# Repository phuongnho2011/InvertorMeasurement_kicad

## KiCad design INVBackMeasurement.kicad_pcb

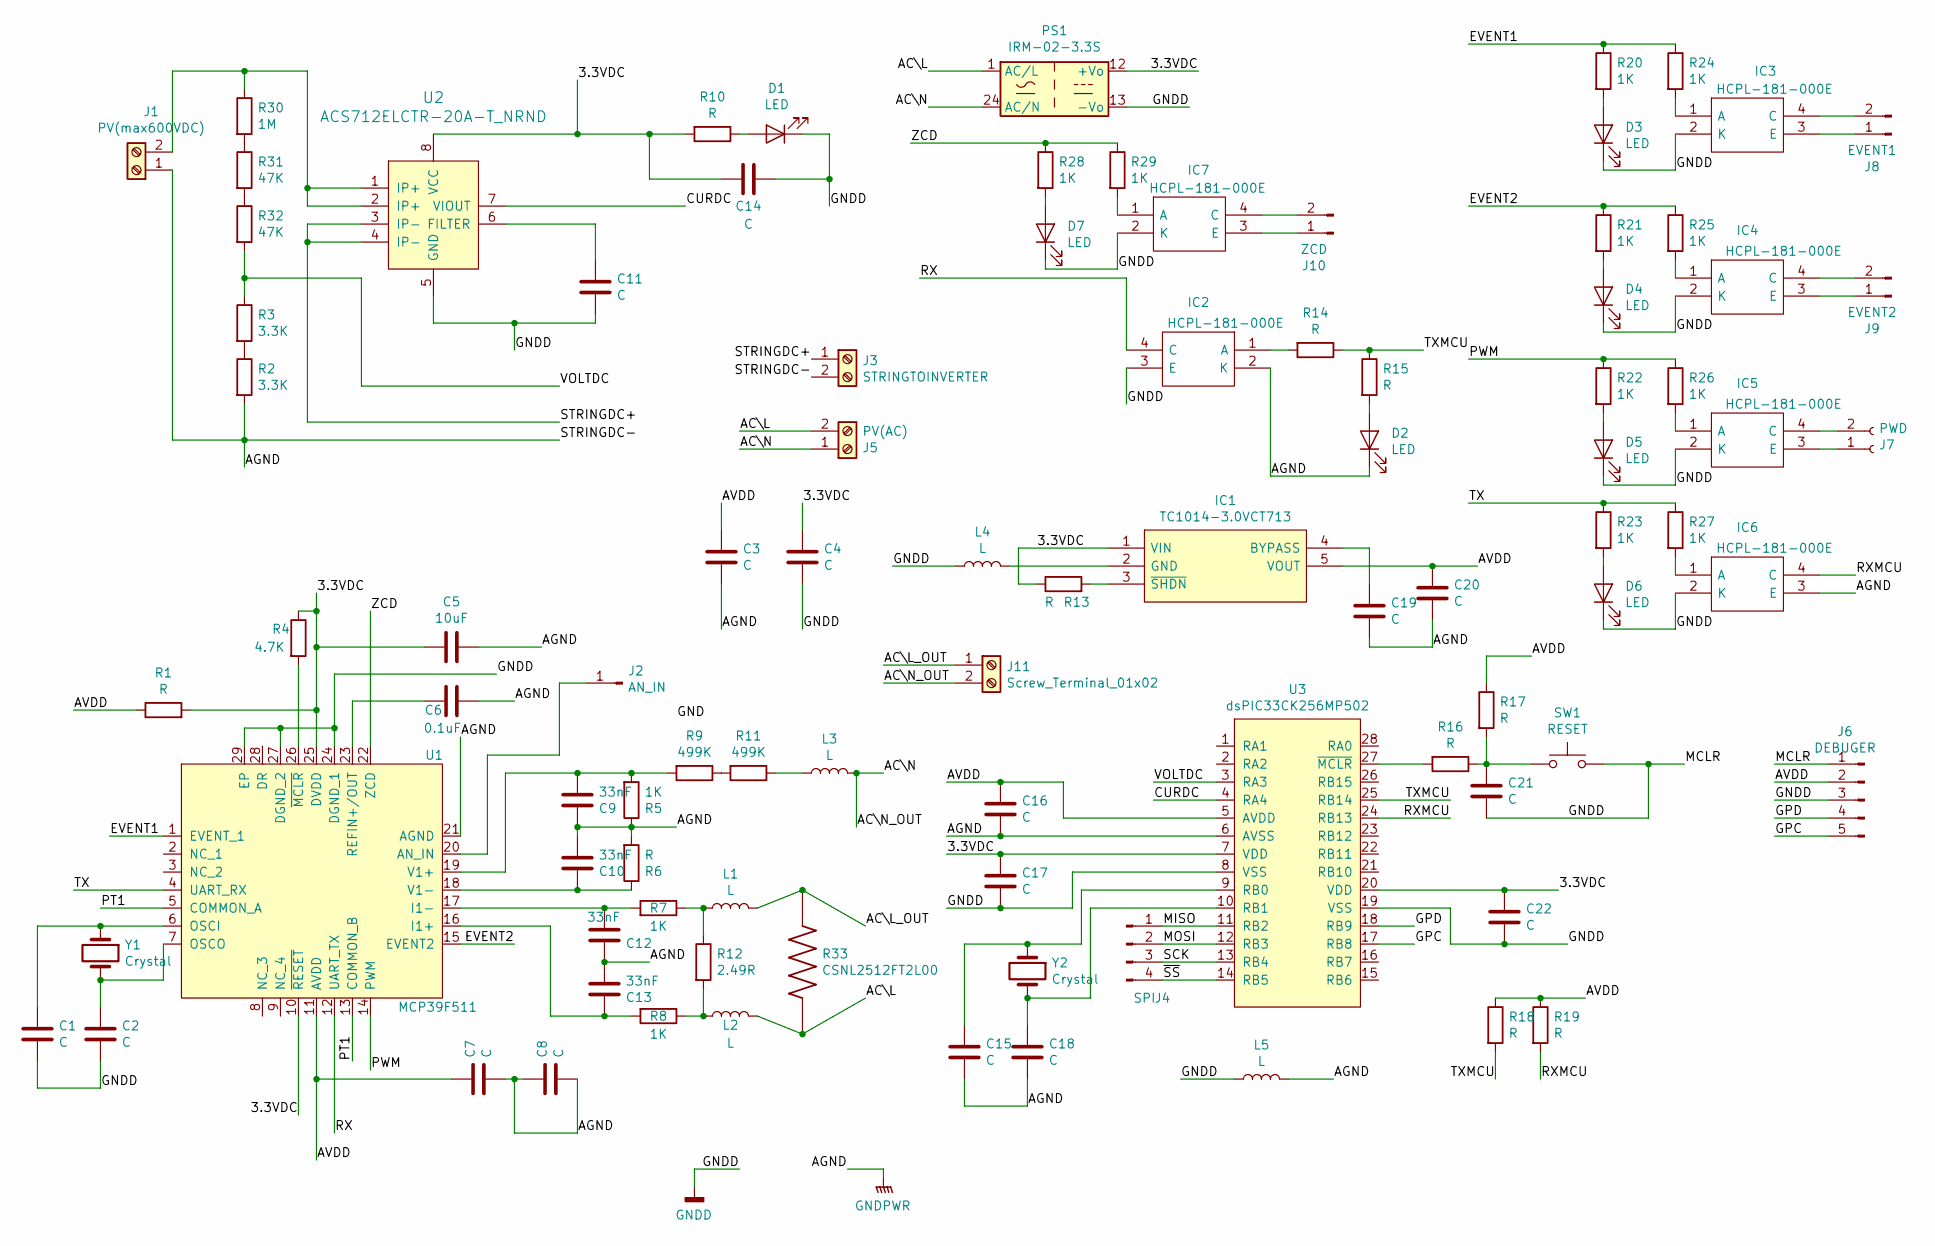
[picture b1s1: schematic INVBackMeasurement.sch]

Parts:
C1, C2, C7, C8, C11, C14, C15, C18, C21: C; C_0805_2012Metric
C3, C4, C16, C17, C19, C20: C; C_1206_3216Metric
C5: 10uF; C_1206_3216Metric
C6: 0.1uF; C_0805_2012Metric
C9, C10, C12, C13: 33nF; C_1206_3216Metric
C22: C; C_1210_3225Metric
D1, D2, D3, D4, D5, D6, D7: LED; LED_0805_2012Metric
IC1: TC1014-3.0VCT713; TC1014-3.0V; Manufacturer_Part_Number TC1014-3.0VCT713; Mouser Part Number 579-TC1014-3.0VCT713
IC2, IC3, IC4, IC5, IC6, IC7: HCPL-181-000E; Manufacturer_Part_Number HCPL-181-000E; Mouser Part Number 630-HCPL-181-000E
J1: PV(max600VDC); TerminalBlock_Wuerth_691311400102_P7.62mm
J2: AN_IN; PinHeader_1x01_P2.54mm_Vertical
J3: STRINGTOINVERTER; TerminalBlock_Wuerth_691311400102_P7.62mm
J4: SPI; PinHeader_1x04_P2.54mm_Vertical
J5: PV(AC); TerminalBlock_Wuerth_691311400102_P7.62mm
J6: DEBUGER; PinHeader_1x05_P2.54mm_Vertical
J7: PWD; PinSocket_1x02_P2.54mm_Vertical
J8: EVENT1; PinHeader_1x02_P2.54mm_Vertical
J9: EVENT2; PinHeader_1x02_P2.54mm_Vertical
J10: ZCD; PinHeader_1x02_P2.54mm_Vertical
J11: Screw_Terminal_01x02; TerminalBlock_Wuerth_691311400102_P7.62mm
L1, L2, L3, L5: L; L_1206_3216Metric
L4: L; L_0805_2012Metric
PS1: IRM-02-3.3S; Converter_ACDC_MeanWell_IRM-02-xx_SMD
R1, R6: R; R_1206_3216Metric
R2, R3: 3.3K; R_1206_3216Metric
R4: 4.7K; R_1206_3216Metric
R5, R7, R8: 1K; R_1206_3216Metric
R9, R11: 499K; R_1206_3216Metric
R10, R13, R14, R15, R16, R17, R18, R19: R; R_0805_2012Metric
R12: 2.49R; R_0805_2012Metric
R20, R21, R22, R23, R24, R25, R26, R27, R28, R29: 1K; R_0805_2012Metric
R30: 1M; R_1206_3216Metric
R31, R32: 47K; R_1206_3216Metric
R33: CSNL2512FT2L00; ShuntMF0.0002Ohm2512
SW1: RESET; SW_PUSH_6mm_H5mm
U1: MCP39F511
U2: ACS712ELCTR-20A-T_NRND; ACS712ELCTR-20A-T; MPN ACS712ELCTR-20A-T; Digi-Key_PN 620-1190-1-ND
U3: dsPIC33CK256MP502
Y1, Y2: Crystal; Crystal_HC49-U_Vertical

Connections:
/3.3VDC: C4.1, C5.2, C14.2, C17.1, C22.1, IC1.1 (VIN), PS1.12 (+Vo), R1.2, R4.1, R10.2, R13.1, U1.10 (~RESET), U1.25 (DVDD), U2.8 (VCC), U3.7 (VDD), U3.20 (VDD)
/AC\L: J5.2, L2.2, PS1.1 (AC/L), R33.2
/AC\L_OUT: J11.1, L1.2, R33.1
/AC\N: J5.1, J11.2, L3.2, PS1.24 (AC/N)
/AVDD: C3.1, C7.1, C16.1, C20.1, IC1.5 (VOUT), J6.2, R1.1, R17.1, R18.1, R19.1, U1.11 (AVDD), U3.5 (AVDD)
/CURDC: U2.7 (VIOUT), U3.4 (RA4)
/EVENT1: R20.1, R24.1, U1.1 (EVENT_1)
/EVENT2: R21.1, R25.1, U1.15 (EVENT2)
/GPC: J6.5, U3.17 (RB8)
/GPD: J6.4, U3.18 (RB9)
/MISO: J4.1, U3.11 (RB2)
/MOSI: J4.2, U3.12 (RB3)
/PT1: U1.5 (COMMON_A), U1.13 (COMMON_B)
/PWM: R22.1, R26.1, U1.14 (PWM)
/RX: IC2.4 (C), U1.12 (UART_TX)
/RXMCU: IC6.4 (C), R19.2, U3.24 (RB13)
/SCK: J4.3, U3.13 (RB4)
/STRINGDC+: J3.1, U2.3 (IP-), U2.4 (IP-)
/TX: R23.1, R27.1, U1.4 (UART_RX)
/TXMCU: R14.1, R15.1, R18.2, U3.25 (RB14)
/VOLTDC: R3.1, R32.2, U3.3 (RA3)
/ZCD: R28.1, R29.1, U1.22 (ZCD)
/~SS: J4.4, U3.14 (RB5)
GNDD: C1.2, C2.2, C4.2, C11.2, C14.1, C17.2, C21.2, C22.2, D1.1 (K), D3.1 (K), D4.1 (K), D5.1 (K), D6.1 (K), D7.1 (K), IC2.3 (E), IC3.2 (K), IC4.2 (K), IC5.2 (K), IC6.2 (K), IC7.2 (K), J6.1, J6.3, L4.1, L5.1, PS1.13 (-Vo), SW1.2, U1.24 (DGND_1), U1.27 (DGND_2), U1.29 (EP), U2.5 (GND), U3.8 (VSS), U3.19 (VSS)
GNDPWR: C3.2, C5.1, C6.1, C7.2, C8.1, C8.2, C9.1, C10.2, C12.1, C13.2, C15.2, C16.2, C18.2, C19.2, C20.2, D2.1 (K), IC2.2 (K), IC6.3 (E), J1.1, J3.2, L5.2, R2.2, R5.1, R6.2, U1.21 (AGND), U3.6 (AVSS)
unnamed: C1.1, U1.6 (OSCI), Y1.1
unnamed: C2.1, U1.7 (OSCO), Y1.2
unnamed: C6.2, U1.23 (REFIN+/OUT)
unnamed: C9.2, R5.2, R9.2, U1.19 (V1+)
unnamed: C10.1, R6.1, U1.18 (V1-)
unnamed: C11.1, U2.6 (FILTER)
unnamed: C12.2, R7.2, U1.17 (I1-)
unnamed: C13.1, R8.2, U1.16 (I1+)
unnamed: C15.1, U3.9 (RB0), Y2.1
unnamed: C18.1, U3.10 (RB1), Y2.2
unnamed: C19.1, IC1.4 (BYPASS)
unnamed: C21.1, R16.1, R17.2, SW1.1
unnamed: D1.2 (A), R10.1
unnamed: D2.2 (A), R15.2
unnamed: D3.2 (A), R20.2
unnamed: D4.2 (A), R21.2
unnamed: D5.2 (A), R22.2
unnamed: D6.2 (A), R23.2
unnamed: D7.2 (A), R28.2
unnamed: IC1.2 (GND), L4.2
unnamed: IC1.3 (~SHDN), R13.2
unnamed: IC2.1 (A), R14.2
unnamed: IC3.1 (A), R24.2
unnamed: IC3.3 (E), J8.1
unnamed: IC3.4 (C), J8.2
unnamed: IC4.1 (A), R25.2
unnamed: IC4.3 (E), J9.1
unnamed: IC4.4 (C), J9.2
unnamed: IC5.1 (A), R26.2
unnamed: IC5.3 (E), J7.1
unnamed: IC5.4 (C), J7.2
unnamed: IC6.1 (A), R27.2
unnamed: IC7.1 (A), R29.2
unnamed: IC7.3 (E), J10.1
unnamed: IC7.4 (C), J10.2
unnamed: J1.2, R30.1, U2.1 (IP+), U2.2 (IP+)
unnamed: J2.1, U1.20 (AN_IN)
unnamed: L1.1, R7.1, R12.1
unnamed: L2.1, R8.1, R12.2
unnamed: L3.1, R11.1
unnamed: R2.1, R3.2
unnamed: R4.2, U1.26 (~MCLR)
unnamed: R9.1, R11.2
unnamed: R16.2, U3.27 (~MCLR)
unnamed: R30.2, R31.1
unnamed: R31.2, R32.1

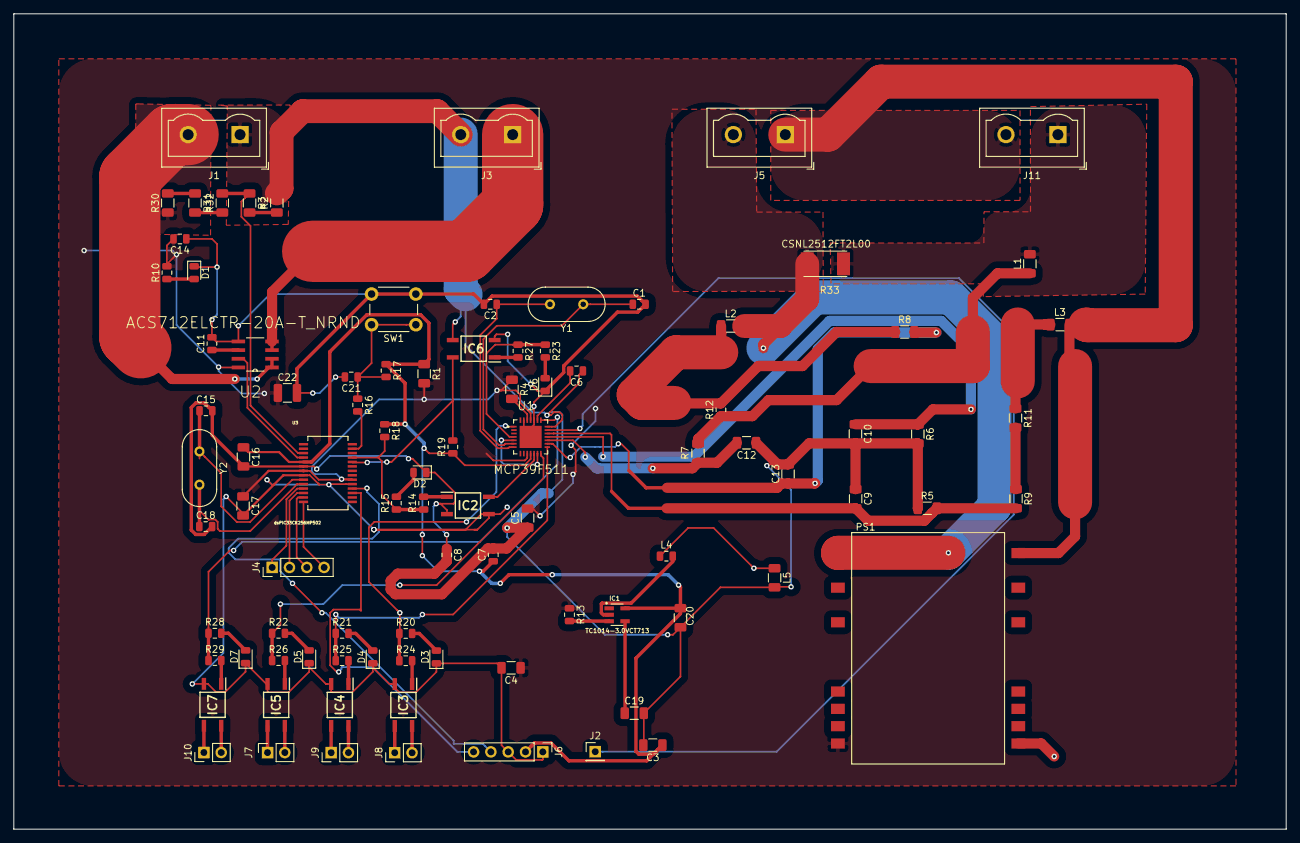
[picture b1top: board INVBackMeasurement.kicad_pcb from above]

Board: 2 copper layers, 186.7 x 119.6 mm, 92 parts (0 on the bottom side), 71 nets.

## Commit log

2019-09-26 the new one
2019-09-26 reorganize one
2019-09-26 reorganize2
2019-09-29 29/9/2019 9:52 PM
2019-10-01 the new one 1/10/2019
2019-10-02 the new one 2/10/2019
2019-10-03 3/10/2019
